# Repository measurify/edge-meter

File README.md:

# Measurify Edge Meter

Edge Measurer is a board based on the [Arduino Nano BLE Sense](https://store.arduino.cc/products/nano-33-ble-sense-rev2?gclid=CjwKCAjwuqiiBhBtEiwATgvixP9YZH3kv_W2rU_MNzxRqpEtBDAPsVifqHgtA1YfRTseUCstFRrMhBoCzdEQAvD_BwE). The board is enhanced with a battery support as in the following figures:

EdgeMeter acquires values from sensors on the Arduino device and exposes the collected data using the on-board BLE connectivity. It provides IMU values (accelerometer, gyroscope and magnetometer), environmental values (proximity, temperature, humidity, pressure and ambient light) and orientation (heading, pitch, roll) as BLE characteristics. The sampling period can be decided by the connected client, the default value is 250 msec.

Two versions of arduino are supported: Change the name in the first line of the file edge-meter.ino as NANO_V1 for **Arduino Nano 33 BLE Sense** or NANO_V2 for **Arduino Nano 33 BLE Sense REV2**.

Folder node-client contains an example of client application developed in NodeJS.

Current version of BLE only allows a maximum of 20 bytes for each message. To send the array of IMU and ENV values we had to convert each value to 16-bit signed integer (int16_t). Sensor resolution is 16 bit so no information is lost. Values are multiplied to a coefficient described below.

The BLE local name is **Mesurify-Meter** and it exposes a single BLE service (UUID: 8e7c2dae-0000-4b0d-b516-f525649c49ca) featuring the following characteristics:

## Sampling Period Characteristic

- UUID: 8e7c2dae-0001-4b0d-b516-f525649c49ca
- Properties: read and write
- Data format: 16-bit unsigned integer
- Values: sampling period in msec

## IMU Characteristic

- UUID: 8e7c2dae-0002-4b0d-b516-f525649c49ca
- Properties: notify
- Original format: array of 9 float
- Data format: array of 9 signed int 16 bit
- Values: acceleration [G] * 8192 , angular velocity [dps] * 16.384 , and magnetic field [uT] * 81.92

## Environment Characteristic

- UUID: 8e7c2dae-0003-4b0d-b516-f525649c49ca
- Properties: notify
- Original format: 3 float and 5 int
- Data format: array of 8 signed int 16 bit
- Values: proximity [0 close, 255 far], temperature [C] * 100 , humidity [%] * 100 , pressure [kPA] * 100 , ambient light [0 dark] and color [RGB]

## Orientation Characteristic

- UUID: 8e7c2dae-0004-4b0d-b516-f525649c49ca
- Properties: notify
- Data format: array of 3 float
- Values: heading [degree], pitch [dpdegrees], and roll [degree]

# Citation
If you find the project helpful, please consider citing our paper:

[1] M. Fresta, A. Dabbous, F. Bellotti, A. Capello, L. Lazzaroni, A. Pighetti, R. Berta.
 **Low-Cost, Edge-Cloud, End-to-End System Architecture for Human Activity Data Collection**. Applications in Electronics Pervading Industry, Environment and Society. ApplePies 2023. Lecture Notes in Electrical Engineering, vol 1110. Springer, Cham. [LINK](https://doi.org/10.1007/978-3-031-48121-5_64)

[2] A. Dabbous, M. Fresta, F. Bellotti, R. Berta. **Neural Architecture for Tennis Shot Classification on Embedded System**. Applications in Electronics Pervading Industry, Environment and Society. ApplePies 2023. Lecture Notes in Electrical Engineering, vol 1110. Springer, Cham. [LINK](https://doi.org/10.1007/978-3-031-48121-5_14)

[3] A. Dabbous, M. Fresta, F. Bellotti, R. Berta. **Arduino Nano-based System for Tennis Shot Classification**. 54th Annual Meeting of the Italian Electronics Society, SIE 2023, Noto, Italy, 2023. [LINK](https://doi.org/10.1007/978-3-031-48711-8_43)

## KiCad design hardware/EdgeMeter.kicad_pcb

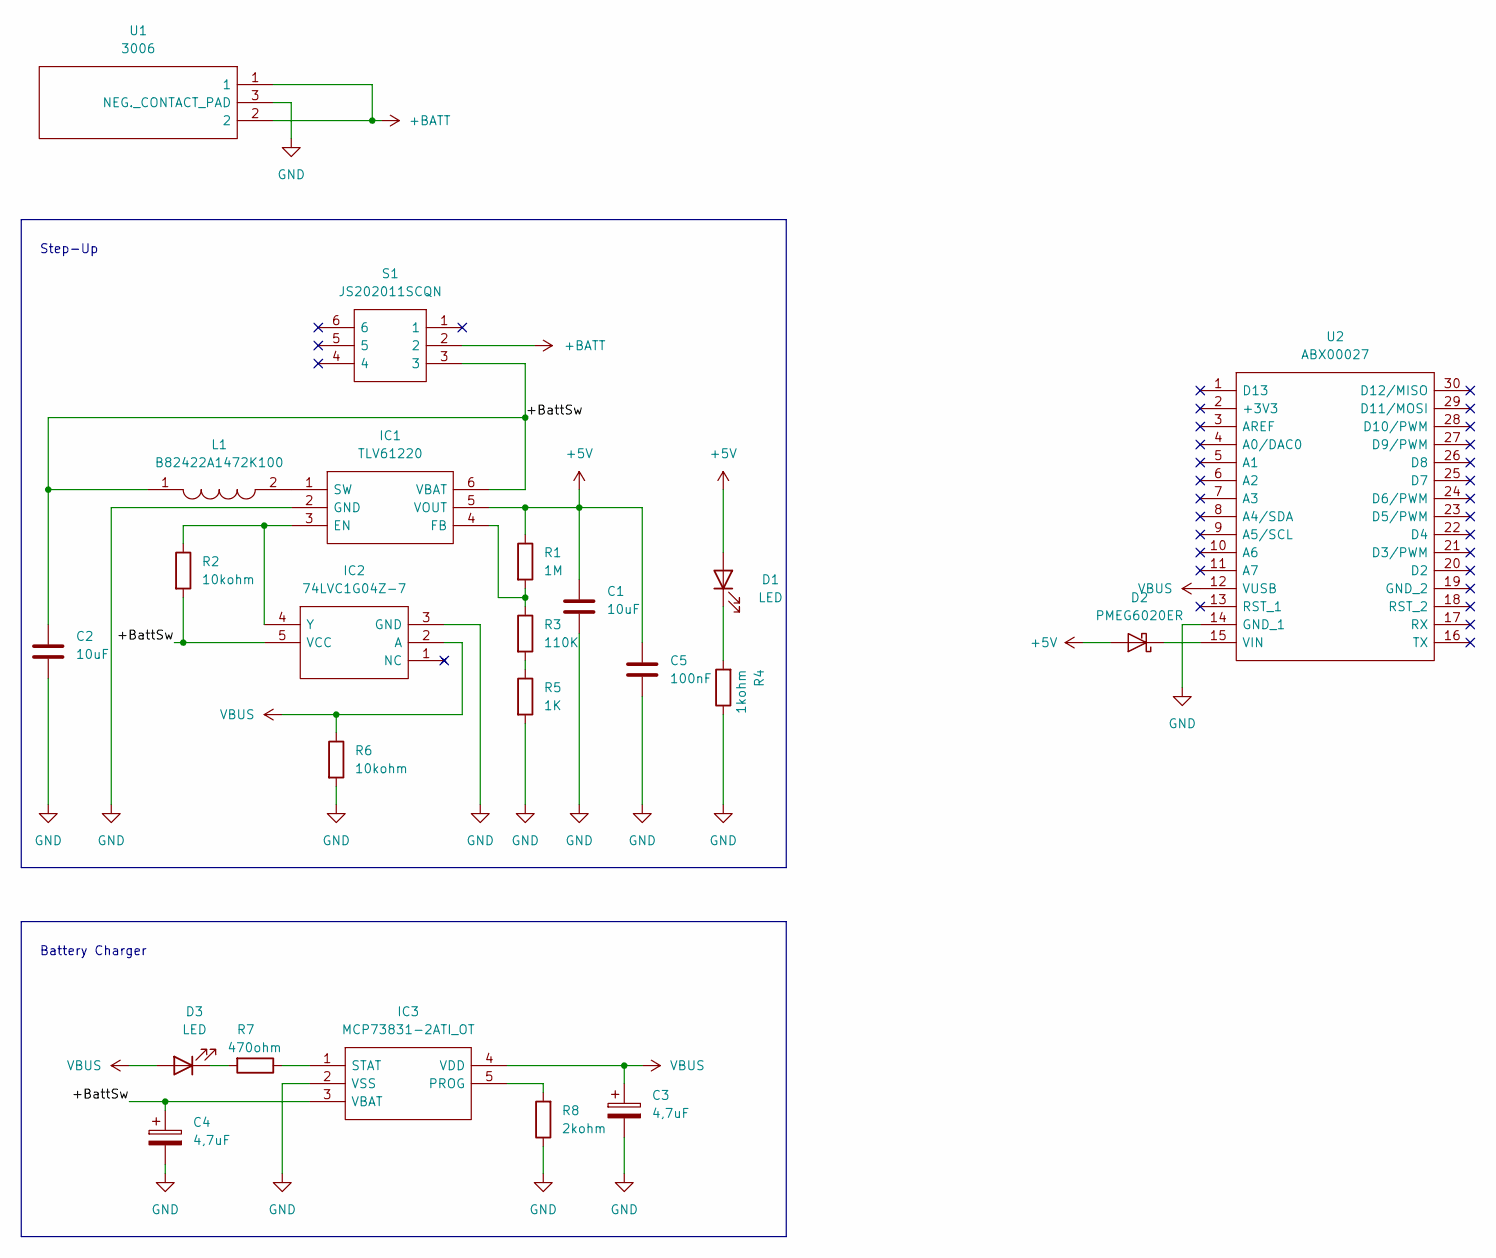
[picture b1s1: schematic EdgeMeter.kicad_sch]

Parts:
C1, C2: 10uF; CP_EIA-3216-18_Kemet-A_Pad1.58x1.35mm_HandSolder
C3, C4: 4,7uF; CP_EIA-3216-18_Kemet-A_Pad1.58x1.35mm_HandSolder
C5: 100nF; C_0805_2012Metric_Pad1.18x1.45mm_HandSolder
D1, D3: LED; LED_0805_2012Metric_Pad1.15x1.40mm_HandSolder
D2: PMEG6020ER; D_SOD-128
IC1: TLV61220; SOT95P280X145-6N; Manufacturer_Part_Number TLV61220
IC2: 74LVC1G04Z-7; SOT-353_SC-70-5_Handsoldering; Manufacturer_Part_Number 74LVC1G04Z-7; Mouser Part Number 621-74LVC1G04Z-7
IC3: MCP73831-2ATI_OT; SOT95P270X145-5N; Manufacturer_Part_Number MCP73831-2ATI/OT
L1: B82422A1472K100; INDC3225X210N; Manufacturer_Part_Number B82422A1472K100; Mouser Part Number 871-B82422A1472K100
R1: 1M; R_0805_2012Metric_Pad1.20x1.40mm_HandSolder
R2, R6: 10kohm; R_0805_2012Metric_Pad1.20x1.40mm_HandSolder
R3: 110K; R_0805_2012Metric_Pad1.20x1.40mm_HandSolder
R4: 1kohm; R_0805_2012Metric_Pad1.20x1.40mm_HandSolder
R5: 1K; R_0805_2012Metric_Pad1.20x1.40mm_HandSolder
R7: 470ohm; R_0805_2012Metric_Pad1.20x1.40mm_HandSolder
R8: 2kohm; R_0805_2012Metric_Pad1.20x1.40mm_HandSolder
S1: JS202011SCQN; Manufacturer_Part_Number JS202011SCQN; Mouser Part Number 611-JS202011SCQN
U1: 3006; Manufacturer_Part_Number 3006; Mouser Part Number 534-3006
U2: ABX00027; Manufacturer_Part_Number ABX00027; Mouser Part Number 782-ABX00027

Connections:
+5V: C1.1, C5.1, D1.2 (A), D2.2 (A), IC1.5 (VOUT), R1.1
+BATT: S1.2, U1.1, U1.2
/+BattSw: C2.1, C4.1, IC1.6 (VBAT), IC2.5 (VCC), IC3.3 (VBAT), L1.1, R2.2, S1.3
GND: C1.2, C2.2, C3.2, C4.2, C5.2, IC1.2 (GND), IC2.3 (GND), IC3.2 (VSS), R4.1, R5.2, R6.2, R8.1, U1.3 (NEG._CONTACT_PAD), U2.14 (GND_1)
unnamed: D1.1 (K), R4.2
unnamed: D2.1 (K), U2.15 (VIN)
unnamed: D3.1 (K), R7.2
unnamed: IC1.1 (SW), L1.2
unnamed: IC1.3 (EN), IC2.4 (Y), R2.1
unnamed: IC1.4 (FB), R1.2, R3.1
unnamed: IC3.1 (STAT), R7.1
unnamed: IC3.5 (PROG), R8.2
unnamed: R3.2, R5.1
VBUS: C3.1, D3.2 (A), IC2.2 (A), IC3.4 (VDD), R6.1, U2.12 (VUSB)

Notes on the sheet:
Battery Charger
Step-Up

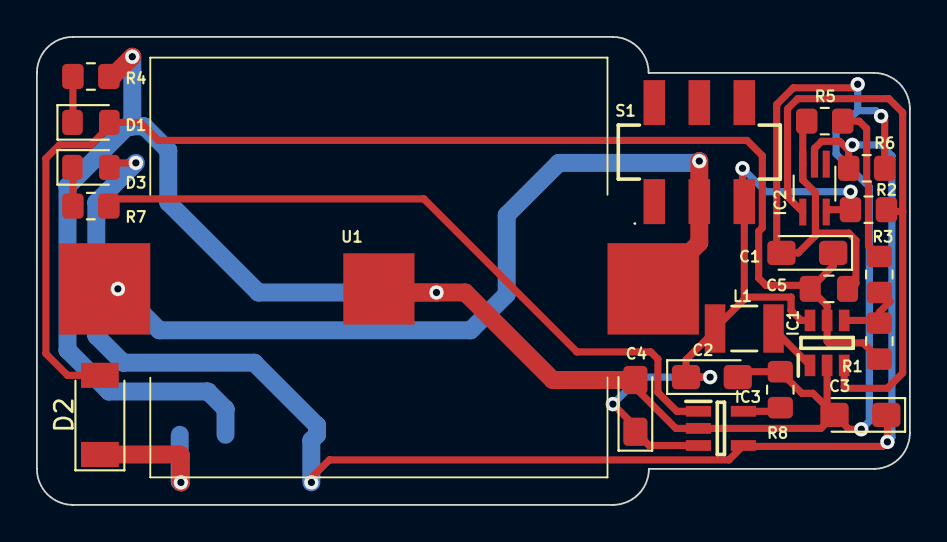
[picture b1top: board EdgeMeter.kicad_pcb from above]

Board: 2 copper layers, 48.5 x 26.0 mm, 23 parts (1 on the bottom side), 14 nets.

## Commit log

2023-04-28 added README
2023-04-28 fixed UUIDs
2023-05-09 added hardware and node client
2023-06-05 Added support for NANO R2
2023-06-05 added orientation characteristic
2023-07-07 Changed size of Characteristics to send less than 20 bytes
2024-02-21 Updated README and changed sampling rate to 100
